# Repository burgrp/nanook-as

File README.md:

# nanook-as
NANOOK analog sensors board

Temperature sensor divider R2=4k7 calculated for range:

|   | temp  |R1 (NTC 3950/10k) |  R2 | Vout   |
|---|-------|------------------|-----|--------|
|min| -24°C | 110k             | 4k7 | 102mV  |
|max| 175°C | 0.1027k          | 4k7 | 2446mV |

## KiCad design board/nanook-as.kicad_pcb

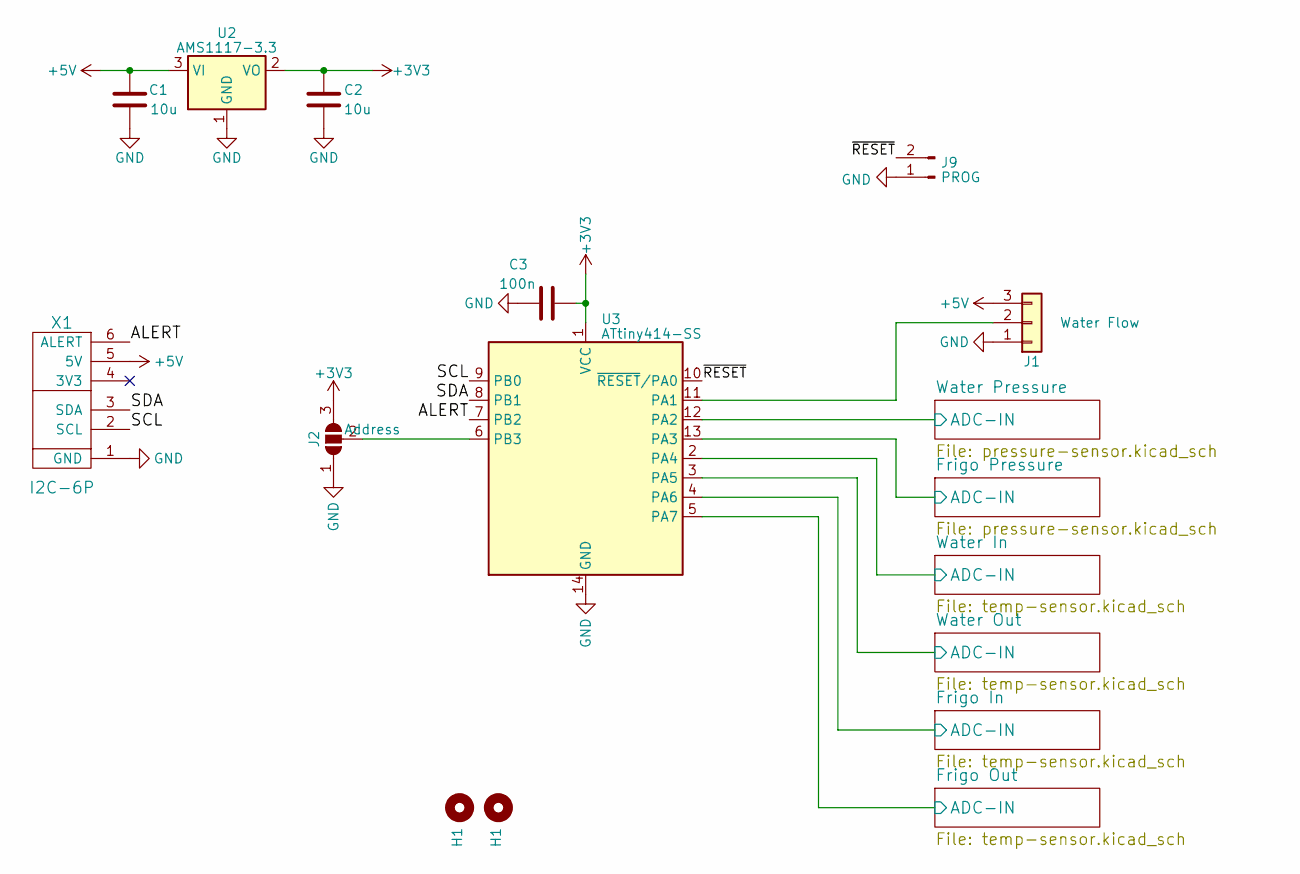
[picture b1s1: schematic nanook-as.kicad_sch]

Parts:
C1, C2: 10u; C_0805_2012Metric
C3: 100n; C_0805_2012Metric
H1: MountingHole; MountingHole_2.2mm_M2_Pad_Via
J1: Water Flow; JST_XH_S3B-XH-A-1_1x03_P2.50mm_Horizontal
J2: Address; SolderJumper-3_P1.3mm_Open_Pad1.0x1.5mm
J9: PROG; PinHeader_1x02_P2.54mm_Vertical
U2: AMS1117-3.3; SOT-223-3_TabPin2
U3: ATtiny414-SS; SOIC-14_3.9x8.7mm_P1.27mm
X1: I2C-6P; Micro-Match-FOB-6

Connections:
+3V3: C2.1, C3.1, J2.3 (B), U2.2 (VO), U3.1 (VCC); also elsewhere on the board
+5V: C1.2, J1.3, U2.3 (VI), X1.5 (5V); also elsewhere on the board
/ALERT: U3.7 (PB2), X1.6 (ALERT)
/Frigo In/ADC-IN: U3.4 (PA6); also elsewhere on the board
/Frigo Out/ADC-IN: U3.5 (PA7); also elsewhere on the board
/Frigo Pressure/ADC-IN: U3.13 (PA3); also elsewhere on the board
/SCL: U3.9 (PB0), X1.2 (SCL)
/SDA: U3.8 (PB1), X1.3 (SDA)
/Water In/ADC-IN: U3.2 (PA4); also elsewhere on the board
/Water Out/ADC-IN: U3.3 (PA5); also elsewhere on the board
/Water Pressure/ADC-IN: U3.12 (PA2); also elsewhere on the board
/~RESET: J9.2, U3.10 (~RESET/PA0)
GND: C1.1, C2.2, C3.2, J1.1, J2.1 (A), J9.1, U2.1 (GND), U3.14 (GND), X1.1 (GND); also elsewhere on the board
unnamed: J1.2, U3.11 (PA1)
unnamed: J2.2 (C), U3.6 (PB3)

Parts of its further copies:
H2: MountingHole; MountingHole_2.2mm_M2_Pad_Via

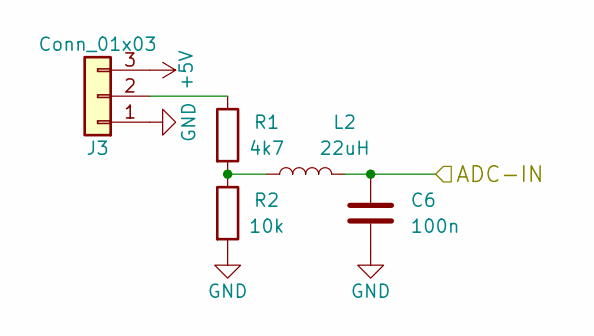
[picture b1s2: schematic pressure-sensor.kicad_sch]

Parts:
C6: 100n; C_0805_2012Metric
J3: Conn_01x03; JST_XH_S3B-XH-A-1_1x03_P2.50mm_Horizontal
L2: 22uH; L_0805_2012Metric
R1: 4k7; R_0805_2012Metric
R2: 10k; R_0805_2012Metric

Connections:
+5V: J3.3; also elsewhere on the board
/Water Pressure/ADC-IN: C6.1, L2.2; also elsewhere on the board
GND: C6.2, J3.1, R2.2; also elsewhere on the board
unnamed: J3.2, R1.1
unnamed: L2.1, R1.2, R2.1

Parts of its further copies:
C7: 100n; C_0805_2012Metric
J4: Conn_01x03; JST_XH_S3B-XH-A-1_1x03_P2.50mm_Horizontal
L3: 22uH; L_0805_2012Metric
R3: 4k7; R_0805_2012Metric
R4: 10k; R_0805_2012Metric

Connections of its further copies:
+5V: J4.3; also elsewhere on the board
/Frigo Pressure/ADC-IN: C7.1, L3.2; also elsewhere on the board
GND: C7.2, J4.1, R4.2; also elsewhere on the board
unnamed: J4.2, R3.1
unnamed: L3.1, R3.2, R4.1

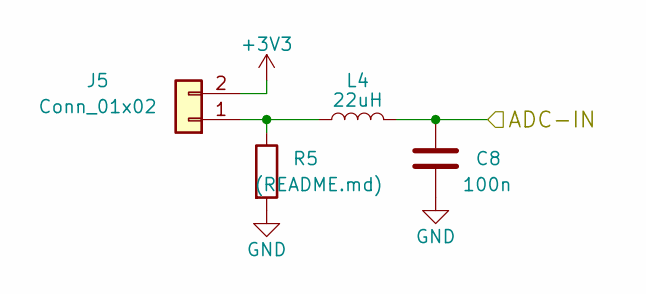
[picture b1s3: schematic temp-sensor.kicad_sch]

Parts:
C8: 100n; C_0805_2012Metric
J5: Conn_01x02; JST_XH_S2B-XH-A-1_1x02_P2.50mm_Horizontal
L4: 22uH; L_0805_2012Metric
R5: (README.md); R_0805_2012Metric

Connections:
+3V3: J5.2; also elsewhere on the board
/Water In/ADC-IN: C8.1, L4.2; also elsewhere on the board
GND: C8.2, R5.2; also elsewhere on the board
unnamed: J5.1, L4.1, R5.1

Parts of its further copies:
C9, C10, C11: 100n; C_0805_2012Metric
J6, J7, J8: Conn_01x02; JST_XH_S2B-XH-A-1_1x02_P2.50mm_Horizontal
L5, L6, L7: 22uH; L_0805_2012Metric
R6, R7, R8: (README.md); R_0805_2012Metric

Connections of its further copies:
+3V3: J6.2, J7.2, J8.2; also elsewhere on the board
/Frigo In/ADC-IN: C10.1, L6.2; also elsewhere on the board
/Frigo Out/ADC-IN: C11.1, L7.2; also elsewhere on the board
/Water Out/ADC-IN: C9.1, L5.2; also elsewhere on the board
GND: C9.2, C10.2, C11.2, R6.2, R7.2, R8.2; also elsewhere on the board
unnamed: J6.1, L5.1, R6.1
unnamed: J7.1, L6.1, R7.1
unnamed: J8.1, L7.1, R8.1

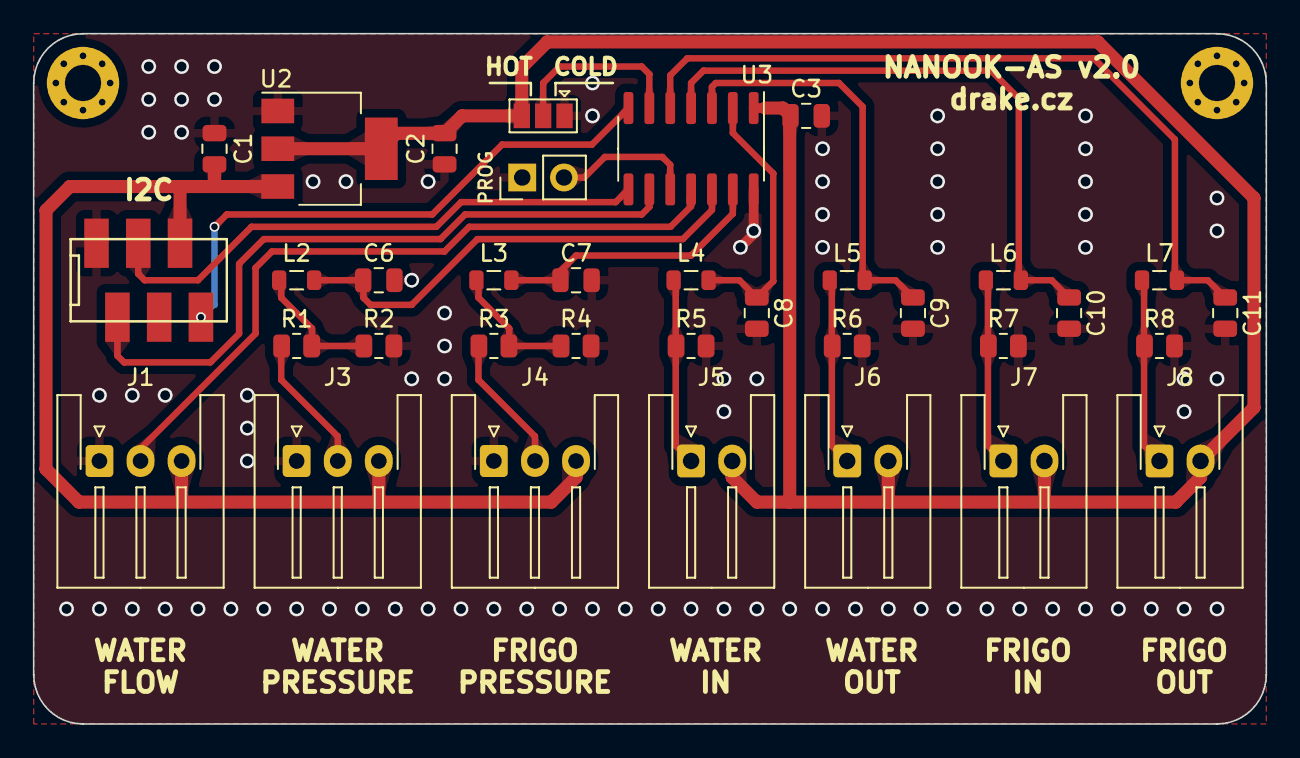
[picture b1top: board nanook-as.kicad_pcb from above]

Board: 2 copper layers, 75.0 x 42.0 mm, 37 parts (0 on the bottom side), 23 nets.

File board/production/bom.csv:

Designator,Footprint,Quantity,Value,LCSC Part #
C1,0805,1,10u,
C10,0805,1,100n,
C11,0805,1,100n,
C2,0805,1,10u,
C3,0805,1,100n,
C6,0805,1,100n,
C7,0805,1,100n,
C8,0805,1,100n,
C9,0805,1,100n,
"H1, H2",MountingHole_2.2mm_M2_Pad_Via,2,MountingHole,
J1,JST_XH_S3B-XH-A-1_1x03_P2.50mm_Horizontal,1,Water Flow,
J2,SolderJumper-3_P1.3mm_Open_Pad1.0x1.5mm,1,Address,
"J3, J4",JST_XH_S3B-XH-A-1_1x03_P2.50mm_Horizontal,2,Conn_01x03,
"J5, J6, J7, J8",JST_XH_S2B-XH-A-1_1x02_P2.50mm_Horizontal,4,Conn_01x02,
J9,PinHeader_1x02_P2.54mm_Vertical,1,PROG,
L2,0805,1,22uH,
L3,0805,1,22uH,
L4,0805,1,22uH,
L5,0805,1,22uH,
L6,0805,1,22uH,
L7,0805,1,22uH,
R1,0805,1,4k7,
R2,0805,1,10k,
R3,0805,1,4k7,
R4,0805,1,10k,
R5,0805,1,(README.md),
R6,0805,1,(README.md),
R7,0805,1,(README.md),
R8,0805,1,(README.md),
U2,SOT-223-3_TabPin2,1,AMS1117-3.3,
U3,SOIC-14_3.9x8.7mm_P1.27mm,1,ATtiny414-SS,
X1,Micro-Match-FOB-6,1,I2C-6P,

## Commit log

2019-01-18 services/1731583
